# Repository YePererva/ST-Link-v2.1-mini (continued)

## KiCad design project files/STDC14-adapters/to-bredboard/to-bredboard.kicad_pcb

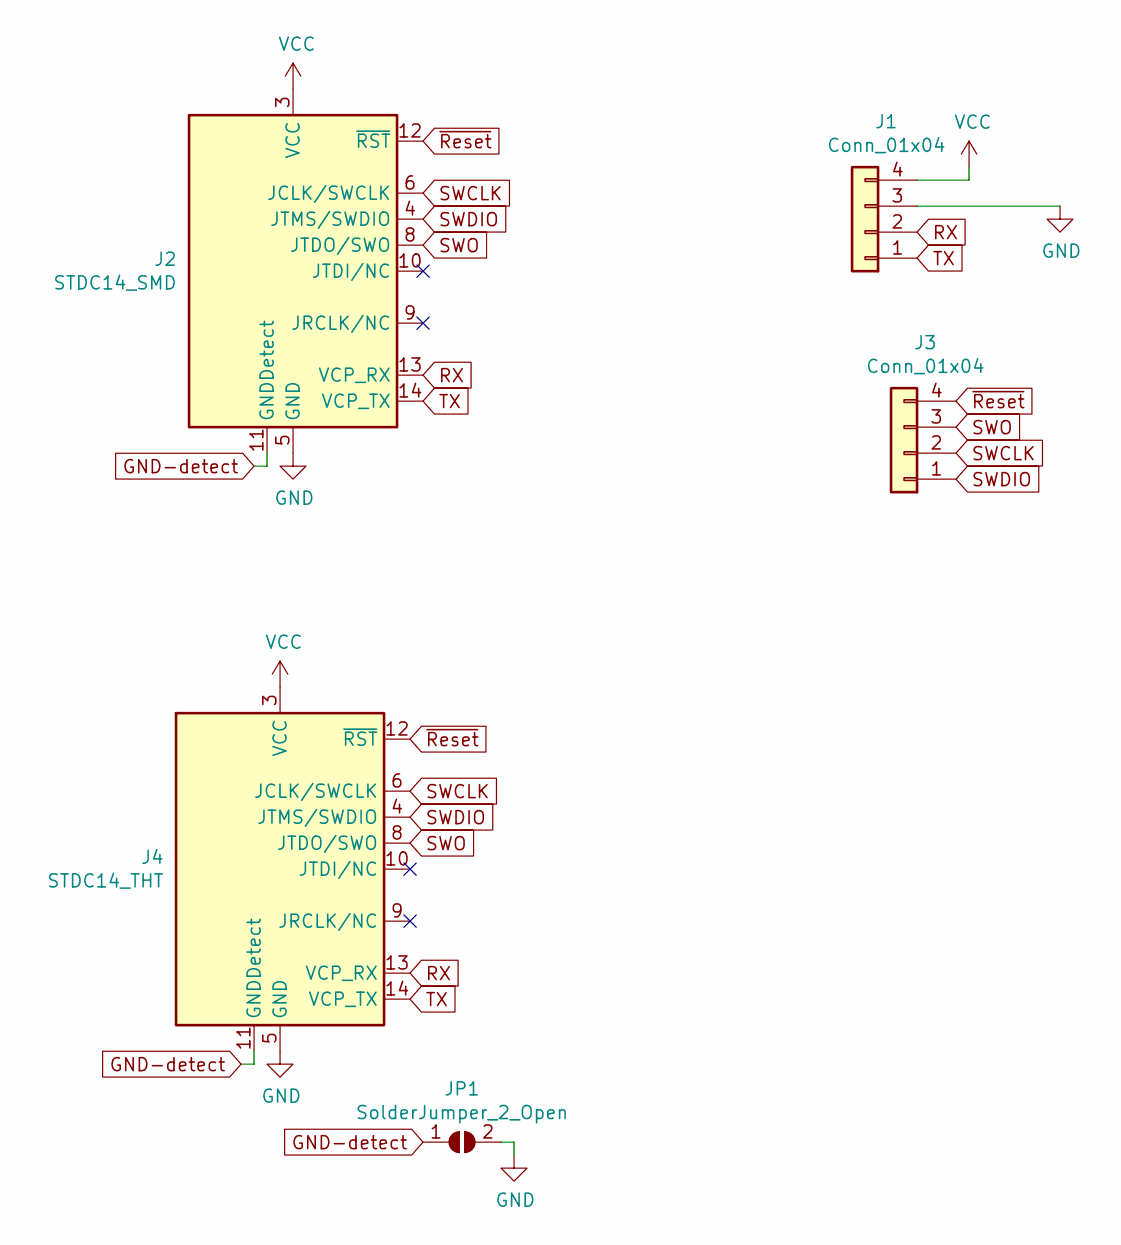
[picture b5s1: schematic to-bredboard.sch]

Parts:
J1, J3: Conn_01x04; PinHeader_1x04_P2.54mm_Vertical
J2: STDC14_SMD; PinHeader_2x07_P1.27mm_Vertical_SMD
J4: STDC14_THT; PinHeader_2x07_P1.27mm_Vertical
JP1: SolderJumper_2_Open; SolderJumper-2_P1.3mm_Open_TrianglePad1.0x1.5mm

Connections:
GND: J1.3, J2.5 (GND), J2.7 (GND), J4.5 (GND), J4.7 (GND), JP1.2 (B)
GND-detect: J2.11 (GNDDetect), J4.11 (GNDDetect), JP1.1 (A)
RX: J1.2, J2.13 (VCP_RX), J4.13 (VCP_RX)
SWCLK: J2.6 (JCLK/SWCLK), J3.2, J4.6 (JCLK/SWCLK)
SWDIO: J2.4 (JTMS/SWDIO), J3.1, J4.4 (JTMS/SWDIO)
SWO: J2.8 (JTDO/SWO), J3.3, J4.8 (JTDO/SWO)
TX: J1.1, J2.14 (VCP_TX), J4.14 (VCP_TX)
VCC: J1.4, J2.3 (VCC), J4.3 (VCC)
~Reset: J2.12 (~RST), J3.4, J4.12 (~RST)

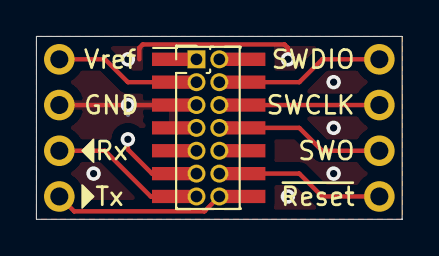
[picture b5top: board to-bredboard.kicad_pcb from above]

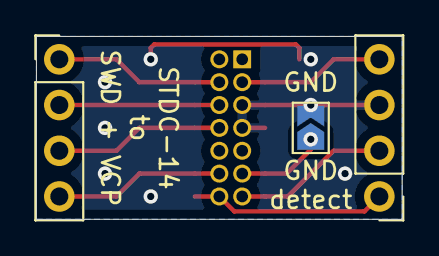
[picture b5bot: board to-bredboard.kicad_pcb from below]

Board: 2 copper layers, 20.3 x 10.2 mm, 5 parts (3 on the bottom side), 9 nets.

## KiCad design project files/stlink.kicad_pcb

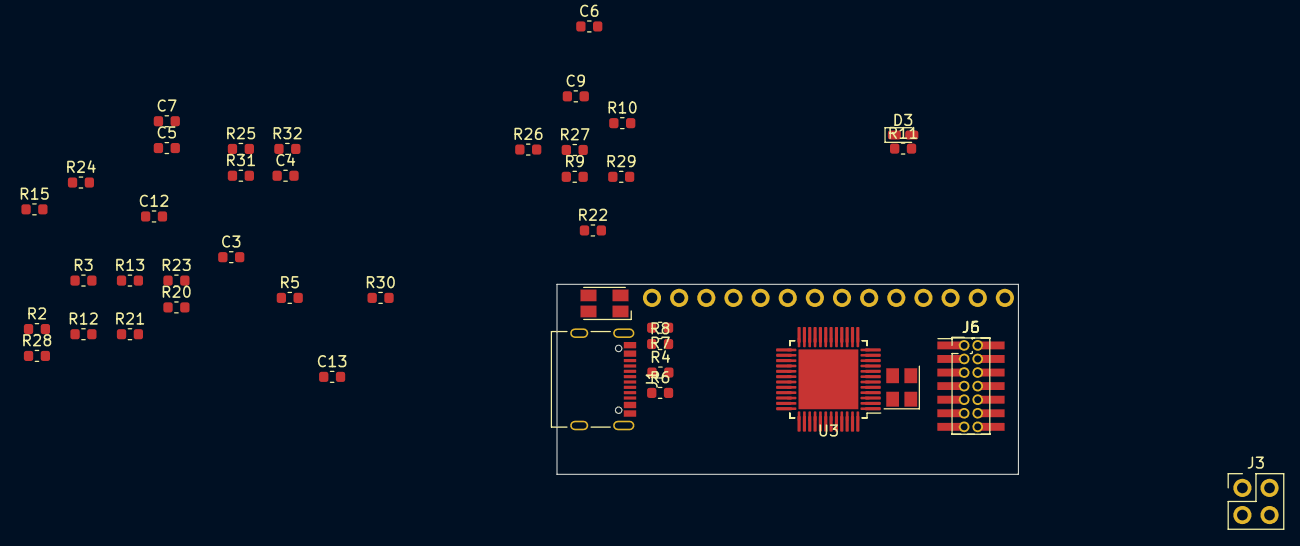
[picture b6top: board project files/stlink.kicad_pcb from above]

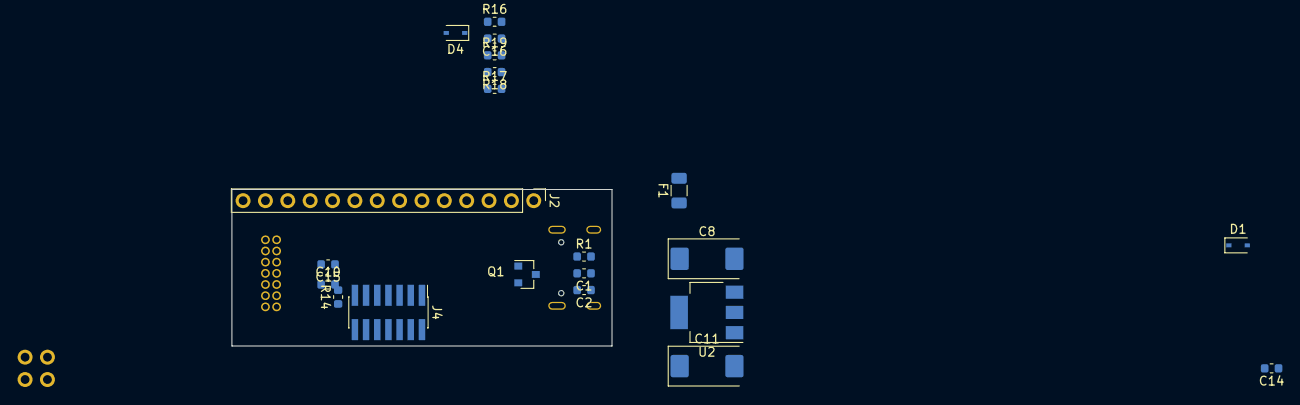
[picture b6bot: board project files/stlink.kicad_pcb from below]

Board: 2 copper layers, 43.2 x 17.8 mm, 64 parts (21 on the bottom side), 51 nets, no tracks yet.

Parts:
C1, C3, C4, C5, C6, C7, C9, C12, C13, C14, C16: 100nF; C_0603_1608Metric
C2: 1nF; C_0603_1608Metric
C8, C11: 22uF; CP_EIA-7343-30_AVX-N
C10, C15: 12pF; C_0603_1608Metric
D1, D4: BAT60A; D_SOD-323
D2: LED_Dual_CACA; LED_Avago_PLCC4_3.2x2.8mm_CW
D3: Power; LED_0603_1608Metric_Castellated
F1: 1A; R_1206_3216Metric
J1: USB Type C; USB_C_Receptacle_Palconn_UTC16-G
J2: Target; PinHeader_1x14_P2.54mm_Vertical
J3: Power Target; PinHeader_2x02_P2.54mm_Vertical
J4: Self; PinHeader_2x07_P1.27mm_Vertical_SMD
J5: Target STDC-14; PinHeader_2x07_P1.27mm_Vertical
J6: Target STDC-14; PinHeader_2x07_P1.27mm_Vertical_SMD
Q1: MMBT9013; SOT-23
R1: 1M; R_0603_1608Metric
R2, R3: 5K1; R_0603_1608Metric
R4: 1K5; R_0603_1608Metric
R5, R6, R26, R27, R28, R29, R30, R31, R32: 22R; R_0603_1608Metric
R7, R14: 10K; R_0603_1608Metric
R8, R17, R22: 100R; R_0603_1608Metric
R9: 36K; R_0603_1608Metric
R10, R11: 330R; R_0603_1608Metric
R12, R13: 100K; R_0603_1608Metric
R15: 1K; R_0603_1608Metric
R16, R18, R19: 4K7; R_0603_1608Metric
R20, R21: 220R; R_0603_1608Metric
R23: 680R; R_0603_1608Metric
R24, R25: 47R; R_0603_1608Metric
U1: STM32F103CBTx; LQFP-48_7x7mm_P0.5mm
U2: AMS1117-3.3; SOT-223-3_TabPin2
U3: STM32F103CBUx; QFN-48-1EP_7x7mm_P0.5mm_EP5.6x5.6mm
Y1: 8MHz; Crystal_SMD_Abracon_ABM8G-4Pin_3.2x2.5mm

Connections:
+3V3: C3.1, C4.1, C5.1, C6.1, C7.1, C11.1, C14.1, D2.4, J3.1, J4.3, Q1.3, R12.2, R15.2, R18.1, R23.2, U1.1, U1.9, U1.24, U1.36, U1.48, U2.2, U3.1, U3.9, U3.24, U3.36, U3.48
+5V: C8.1, C9.1, D1.1, J3.3, R7.1, U2.3
/D+: J1.A6, J1.B6, R4.1, R5.1
/D-: J1.A7, J1.B7, R6.1
AIN: C16.2, R17.1, R18.2, R19.1, U1.10, U3.10
BOOT_0: C13.2, R13.1, U1.44, U3.44
BOOT_1: C1.2, C2.2, C3.2, C4.2, C5.2, C6.2, C7.2, C8.2, C9.2, C10.2, C11.2, C12.1, C13.1, C14.2, C15.2, C16.1, D2.1, D3.1, J1.A1, J1.A12, J1.B1, J1.B12, J2.3, J2.10, J4.5, J4.7, J4.11, J5.5, J5.7, J5.11, J6.5, J6.7, J6.11, R1.1, R2.2, R3.2, R9.1, R13.2, R14.1, R16.2, R19.2, U1.8, U1.20, U1.23, U1.35, U1.47, U2.1, U3.8, U3.20, U3.23, U3.35, U3.47, U3.49, Y1.2, Y1.4
Board_ID: R14.2, U1.2, U3.2
unnamed: C1.1, C2.1, J1.S1, R1.2
unnamed: D1.2, F1.1
unnamed: D2.2, R10.1
unnamed: D2.3, R11.1
unnamed: D3.2, R15.1
unnamed: D4.1, R17.2
unnamed: J1.A5, R2.1
unnamed: J1.B5, R3.1
unnamed: Q1.1, R7.2, R8.2, R9.2
unnamed: Q1.2, R4.2
OSC_IN: C10.1, U1.5, U3.5, Y1.1
OSC_OUT: C15.1, U1.6, U3.6, Y1.3
SELF_NRST: C12.2, J4.12, R12.1, U1.7, U3.7
STLINK_LED: J4.14, R11.2, U1.30, U3.30
STLINK_RX: R31.2, U1.13, U3.13
STLINK_TX: R32.2, U1.12, U3.12
STLINK_USB_D+: R5.2, U1.33, U3.33
STLINK_USB_D-: R6.2, U1.32, U3.32
SWDCLK: J4.6, U1.37, U3.37
SWDIO: J4.4, U1.34, U3.34
SWO: J4.8, U1.39, U3.39
Self_RX(h): J4.13, R29.2, U1.31, U3.31
T_JTDI: R30.2, U1.17, U3.17
T_JTDI(h): J5.10, J6.10, R30.1
T_NRST_SWD: R27.2, U1.18, U3.18
T_NRST_SWD(h): J2.5, J5.12, J6.12, R27.1
T_NRST_SWIM: R21.2, R25.1, U1.42, U3.42
T_NRST_SWIM(h): J2.11, R25.2
T_NRST_SWIM_IN: R21.1, U1.41, U3.41
T_SWDCLK: R28.2, U1.15, U1.26, U3.15, U3.26
T_SWDCLK(h): J2.2, J5.6, J6.6, R28.1
T_SWDIO: R22.2, R26.2, U1.27, U3.27
T_SWDIO(h): J2.4, J5.4, J6.4, R26.1
T_SWDIO_IN: R22.1, U1.25, U3.25
T_SWIM: R20.2, R23.1, R24.1, U1.22, U1.45, U3.22, U3.45
T_SWIM(h): J2.9, R24.2
T_SWIM_IN: R20.1, U1.21, U1.43, U1.46, U3.21, U3.43, U3.46
T_SWO(h): J2.6, J5.8, J6.8, R29.1
T_VCP_RX(h): J2.14, J5.13, J6.13, R32.1
T_VCP_TX(h): J2.13, J5.14, J6.14, R31.1
T_Vref: D4.2, J2.1, J2.8, J3.2, J3.4, J5.3, J6.3, R16.1
USB_RENUMn: R8.1, U1.38, U3.38
VBUS: F1.2, J1.A4, J1.A9, J1.B4, J1.B9

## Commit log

2020-01-07 first draft
2020-01-07 added reference documents
2020-01-07 updates + references
2020-01-07 Added STDC14
2020-01-07 re-arrangements
2020-01-14 ajfdlsa;jd;sakd
2020-01-27 info update
2020-02-12 Added JTAG to STDC14
2020-04-15 USB Type C shield fix
2020-04-17 Added possibility to power target from programmer
2020-04-17 minor tracing
2020-04-20 new references
2020-05-09 added reference for BMP
2020-05-18 multi-sheet introduction for spare parts
2020-06-19 some rerouting
2020-06-26 fixes
2020-07-22 updates with level converters
2020-11-05 fix after re-open in last KiCAD
2020-12-07 Added STDC-14 adaptors
2020-12-07 files re-arrangement
2020-12-09 Self RX/TX fix
2021-01-19 STDC adapters
2021-06-06 re-opened with kicad 5.99
2021-10-08 edited labels according to kicad 5.99
2021-10-08 reopened with fresher kicad
2022-07-09 added new references
2022-11-02 added reference
